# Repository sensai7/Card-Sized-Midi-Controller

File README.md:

# Card Size Midi Controller
 Standard card sized MIDI controller, for level, pan, modulation wheel and control changes. Both hardware and software are open source, you can modify and use as you please.

## Ordering your own board
### Tindie

This device is available at [Tindie](https://www.tindie.com/products/sensai7/card-sized-midi-controller/).

### JLCPCB
This repository includes the necessary files to order your own board with the SMT components pre-soldered from JLCPCB's assembly service. To do so, follow this: 

1. from this Github page click `Code > download zip`.
2. Uncompress the zip.
3. Go to jlcpcb.com or any other pcb maker. I'll assume you're using JLC for the next steps.
4. Select `instant quote` and when prompted to select a gerber file, select the file `\Kicad\CardSizeMidiController\production\CardSizeMidiController.zip`. From here there will be a lot of options but most of them can be left as default. The only “mandatory” change is `Mark on PCB` which should be changed to `Order Number (Specify Position)`. You can also optionaly change:
* the quantity (5 by default)
* the color, which is green by default.
* PCB thickness can also be changed at will but I think too thin or too thick and the price increases a little bit.

If you go like this and checkout the order you will be buying the naked PCBs with nothing mounted. If you want at least to mount the SMT components then:

1. Switch the PCB Assembly on at the bottom of the menu in the JLC order page.
2. Everything can be left on the default values (Top side, Economic, etc) but you can choose to assemble just a couple of boards instead of all of them. It’ll save you some money but you’ll be left with 3 naked boards.
3. Hit next twice and you'll be asked to upload a BOM file and a CPL file. They’re both in the same folder as the gerber zip from before, they’re respectively `bom.csv` and `positions.csv`.
4. Go to the next screen and you’ll see a table with all the components that are about to be assembled.
5. Next screen will show you a 3D render of the board with the components. For some reason Kicad doesn't export all well the positions and angles, so keep an eye on where the things are being placed. Particularly the position of the USB connector, the potentiometers, and the angle of the push buttons.
6. After that screen you can continue until ordering them.

## Writing the firmware

To burn the firmware you'll need an Arduino Uno board or any Arduino that can be used as ISP. 

 1. Upload the Arduino example "Arduino as ISP" to your arduino board.
 2. Unplug the Arduino, connect the ICSP header from the Arduino to the ICSP header of your MIDI controller board, EXCEPT the RST pin from the MIDI controller (third row, first column), which should be connected to the arduino board pin 10.

 3. Check which processor you have. If you have an AtMega328P you can continue, if it's a AtMega328PB you'll need to [change the signature](https://www.instructables.com/How-to-Fix-Expected-Signature-for-ATMEGA328P-Is-1E/) in the avrdude config file.
 3. In tools > Programmer be sure "Arduino as ISP" is selected with a check mark, or otherwhise the following actions will be executed in the Arduino board instead of the target board.
 4. Select the appropiate board/port in the Arduino IDE and go to tools > Burn bootloader. This bootloader will be overwritten in a second, but burning it now will activate some useful fuses inside the microcontroller, particularly the one selecting an external crystal oscillator. This needs to be done only once per chip.
 5. Open the firmware script "\Code\CardSizeMidiController\CardSizeMidiController.ino" or any custom script in the Arduino IDE and holding shift press the upload button, or select Sketch > Upload using uploader. After a few seconds of LED flashing the chip should have the firmware ready.

## How to use (Standard firmware)
Each button selects a different mode. The turned on LEDs signal the active midi channels.

 * When LEVEL mode is activated, each potentiometer change the Level Control Change (0x07) from channels 1 to 6.
 * When PAN mode is activated, each potentiometer change the Pan Control Change (0x0A) from channels 1 to 6.
 * When MOD mode is activated, each potentiometer change the Modulation Wheel Control Change (0x01) from channels 1 to 6.
 * When CC1 mode is activated, each potentiometer change a different unassigned CC value (0x1A,0x1B,0x1C,0x1D,0x1E,0x1F) in the active channel. 
 * When CC1 mode is activated, each potentiometer change a different unassigned CC value (0x66,0x67,0x68,0x69,0x70,0x71) in the active channel. 
 * When CC1 mode is activated, each potentiometer change a different unassigned CC value (0x72,0x73,0x74,0x75,0x76,0x77) in the active channel. 

In the CC modes the midi channel can be changed from 1 to 16 pressing multiple times the same button. The LEDs light up accordingly.
In the LEVEL, PAN, and MOD modes, subsequent presses of the mode button will toggle the active MIDI channels from 1-6 to 7-12.

There are currently three double-button press settings:

 * Holding down buttons 1 and 2 makes the rightmost potentiometer control the value randomness from 0 (not randomness) to 127 (any value possible).
 * Holding down buttons 3 and 4 makes the rightmost potentiometer change the curve for all the MIDI messages from linear to logarithmic.
 * Holding down buttons 5 and 6 makes the rightmost potentiometer control the LED brightness.

Hold down a switch while powering up to select a different CC preset (1~6). Different presets can be flashed via code to accomodate to the CC received by any synthesizer or audio device. Not pressing any switch during boot will result in the default CC preset, which uses the forementioned undefined CC values.

Default presets:

 0. (default) Undefined CC. Use this preset to use along MIDI learn in your devices.
 1. Korg Volca FM preset
 2. Korg Volca Keys preset
 3. Korg Volca Bass preset
 4. Korg Volca Nubass preset
 5. Korg Volca Kick preset
 6. Korg Volca Sample preset

## How to use (Korg NTS-3 firmware)
This firmware allows more functionality when used along with a Korg NTS-3 kaoss pad kit. In this firmware the controls act like follow:

 * Pressing the 1st push button, enters FX1 mode. In this mode the potentiometers change Control changes (16, 48, 17, 49, 18, 50), corresponding to PADX (coarse), PADX (fine), PADY (coarse), PADY (fine), DEPTH (coarse), and DEPTH (fine) respectively, for FX1
 * Pressing buttons 2, 3 and 4 change the mode to FX2, FX3 and FX4 respectively. The potentiometer controls are arranged the same as in FX1 mode except they affect the corresponding mode FX number.
 * Button 5 changes the mode to TOTAL FX mode, the potentiometer controls are arranged the same as in FX1~4 but they affect the total FX.
 * Button 6 changes the mode to MASTER AND SELECTION mode, in this mode the potentiometers control Master Volume (coarse), Master Volume (fine), FX1 SELECTION, FX2 SELECTION, FX3 SELECTION, and FX4 SELECTION respectively.
 * In modes FX1~4, successive button presses freeze and unfreeze the selected FX, this is reflected by the brightness of the selected mode LED.

 Along with the three double-button settings present in the regular firmware (Randomness, linear-log setting, and LED brightness), there are extra double-button controls:

 * While holding Button 5, pressing buttons 1 to 4 toggle FX1 to 4 TOUCH on and off.
 * While holding Button 6, pressing buttons 1 to 4 toggle FX1 to 4 on and off.

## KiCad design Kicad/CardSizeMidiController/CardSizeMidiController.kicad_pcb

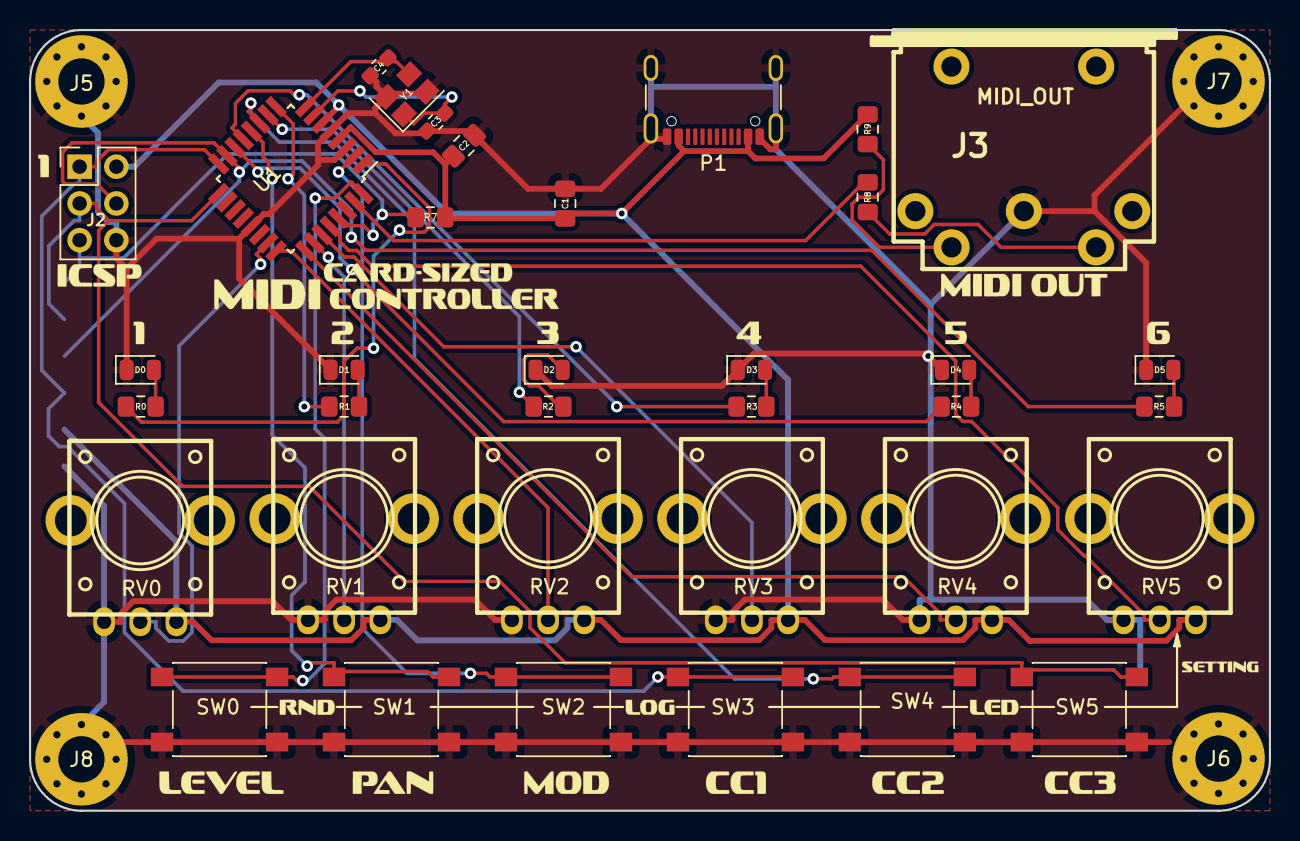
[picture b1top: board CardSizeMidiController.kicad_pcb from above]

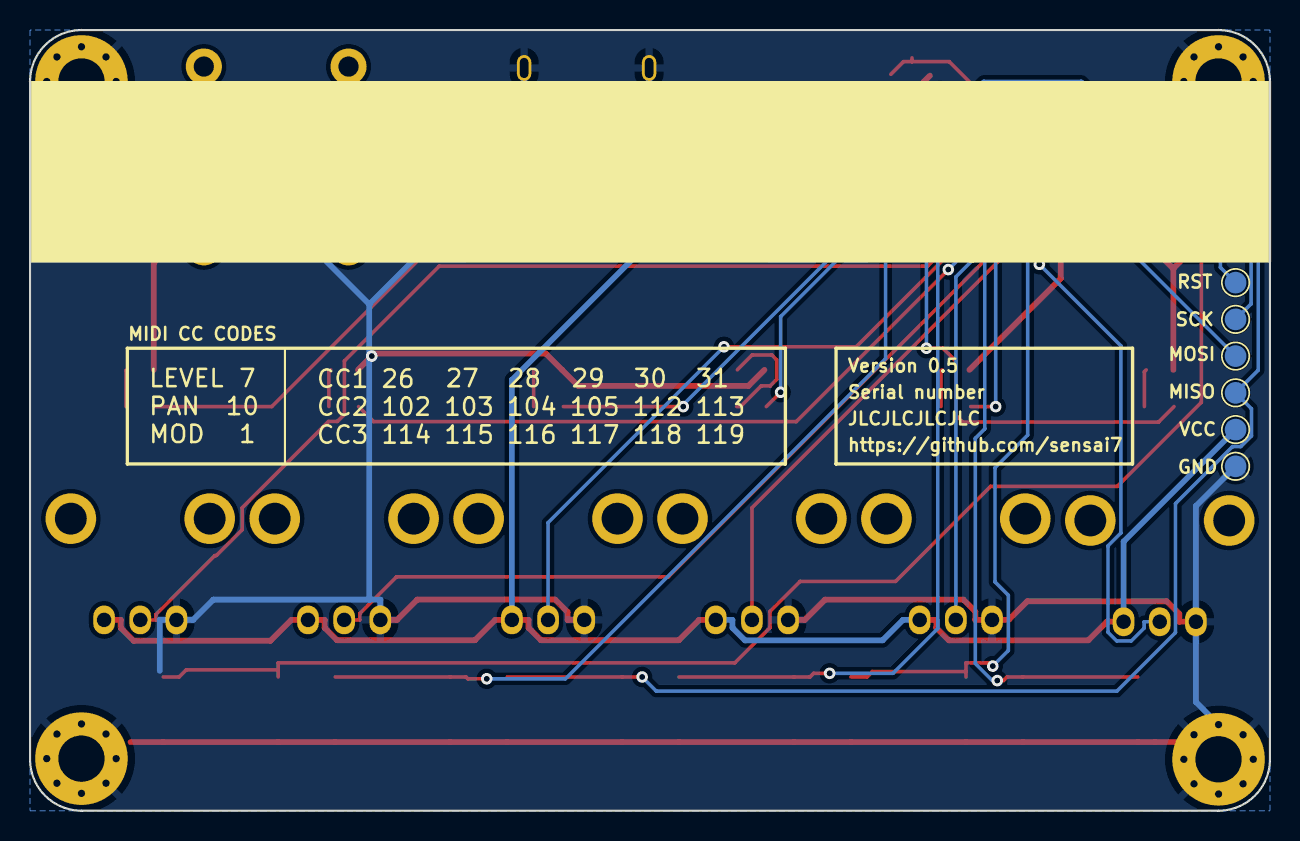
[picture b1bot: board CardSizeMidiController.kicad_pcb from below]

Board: 2 copper layers, 85.7 x 54.0 mm, 66 parts (6 on the bottom side), 32 nets.

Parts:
C1: 100n; C_0805_2012Metric_Pad1.15x1.40mm_HandSolder
C2: 10u; C_0805_2012Metric_Pad1.15x1.40mm_HandSolder
C3, C4: 22p; C_0603_1608Metric_Pad1.05x0.95mm_HandSolder
D0, D1, D2, D3, D4, D5: LED; LED_0805_2012Metric
J2: Conn_02x03_Odd_Even; PinHeader_2x03_P2.54mm_Vertical
J3: MIDI_OUT; din-5
J5, J6, J7, J8: Screw_Terminal_01x01; MountingHole_3.2mm_M3_Pad_Via
LOGO1: Logo_Open_Hardware_Small; card sized midi controller logo
LOGO2: Logo_Open_Hardware_Small; ICSP
LOGO3: Logo_Open_Hardware_Small; midi out
LOGO4: Logo_Open_Hardware_Small; setting
LOGO5: Logo_Open_Hardware_Small; rnd
LOGO6: Logo_Open_Hardware_Small; log
LOGO7: Logo_Open_Hardware_Small; led
LOGO8, LOGO14: Logo_Open_Hardware_Small; 1
LOGO9: Logo_Open_Hardware_Small; 2
LOGO10: Logo_Open_Hardware_Small; 3
LOGO11: Logo_Open_Hardware_Small; 4
LOGO12: Logo_Open_Hardware_Small; 5
LOGO13: Logo_Open_Hardware_Small; 6
LOGO15: Logo_Open_Hardware_Small; level
LOGO16: Logo_Open_Hardware_Small; pan
LOGO17: Logo_Open_Hardware_Small; mod
LOGO18: Logo_Open_Hardware_Small; cc1
LOGO19: Logo_Open_Hardware_Small; cc2
LOGO20: Logo_Open_Hardware_Small; cc3
P1: USB_C_Plug_USB2.0; USB_C_Receptacle_GCT_USB4105-xx-A_16P_TopMnt_Horizontal
R0, R1, R2, R3, R4, R5: 1k; R_0805_2012Metric_Pad1.15x1.40mm_HandSolder
R7: 10k; R_0805_2012Metric_Pad1.15x1.40mm_HandSolder
R8, R9: 220R; R_0805_2012Metric_Pad1.15x1.40mm_HandSolder
RV0, RV1, RV2, RV3, RV4, RV5: 5k; trimmer_alps-rk09k1130ah1
SW0, SW1, SW2, SW3, SW4, SW5: SW_Push; SW_Push_1P1T_NO_6x6mm_H9.5mm
TP1, TP2, TP3, TP4, TP5, TP6: TestPoint; TestPoint_Pad_D1.5mm
U1: ATmega328P-AU; TQFP-32_7x7mm_P0.8mm
Y1: 16MHz; Crystal_SMD_3225-4Pin_3.2x2.5mm

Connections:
+5V: C1.1, C2.1, J2.2, P1.A4 (VBUS), P1.A9 (VBUS), P1.B4 (VBUS), P1.B9 (VBUS), R7.1, R9.1, RV0.3, RV1.3, RV2.3, RV3.3, RV4.3, RV5.3, TP4.1, U1.4 (VCC), U1.6 (VCC)
A0: RV0.2, U1.23 (PC0)
A1: RV2.2, U1.24 (PC1)
A2: RV4.2, U1.25 (PC2)
A3: RV1.2, U1.26 (PC3)
A4: RV3.2, U1.27 (PC4)
A5: RV5.2, U1.28 (PC5)
GND: C1.2, C2.2, C3.1, C4.2, D0.1 (K), D1.1 (K), D2.1 (K), D3.1 (K), D4.1 (K), D5.1 (K), J2.6, J3.2, J5.1, J6.1, J7.1, J8.1, P1.A1 (GND), P1.A12 (GND), P1.B1 (GND), P1.B12 (GND), P1.S1 (SHIELD), RV0.1, RV1.1, RV2.1, RV3.1, RV4.1, RV5.1, SW0.2, SW1.2, SW2.2, SW3.2, SW4.2, SW5.2, TP6.1, U1.3 (GND), U1.5 (GND), U1.21 (GND), Y1.2, Y1.4
LED0: R0.1, U1.1 (PD3)
LED1: R1.1, U1.9 (PD5)
LED2: R2.1, U1.10 (PD6)
LED3: R3.1, U1.13 (PB1)
LED4: R4.1, U1.14 (PB2)
LED5: J2.4, R5.1, TP5.1, U1.15 (PB3)
MISO: J2.1, SW3.1, TP1.1, U1.16 (PB4)
unnamed: D0.2 (A), R0.2
unnamed: D1.2 (A), R1.2
unnamed: D2.2 (A), R2.2
unnamed: D3.2 (A), R3.2
unnamed: D4.2 (A), R4.2
unnamed: D5.2 (A), R5.2
unnamed: J3.4, R9.2
unnamed: J3.5, R8.1
SCK: J2.3, SW5.1, TP2.1, U1.17 (PB5)
SW0: SW0.1, U1.32 (PD2)
SW1: SW2.1, U1.2 (PD4)
SW2: SW4.1, U1.11 (PD7)
SW3: SW1.1, U1.12 (PB0)
TX: R8.2, U1.31 (PD1)
XTAL1: C3.2, U1.7 (XTAL1/PB6), Y1.1
XTAL2: C4.1, U1.8 (XTAL2/PB7), Y1.3
~RST: J2.5, R7.2, TP3.1, U1.29 (~RESET/PC6)

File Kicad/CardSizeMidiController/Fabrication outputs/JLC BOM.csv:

Comment,Designator,Footprint,LCSC
100n,C1,Capacitor_SMD:C_0805_2012Metric_Pad1.15x1.40mm_HandSolder,C49678
10u,C2,Capacitor_SMD:C_0805_2012Metric_Pad1.15x1.40mm_HandSolder,C15850
22p,"C3,C4",Capacitor_SMD:C_0603_1608Metric_Pad1.05x0.95mm_HandSolder,C1653
LED,"D0,D1,D2,D3,D4,D5",LED_SMD:LED_0805_2012Metric,C34499
USB_B,J1,Connector_USB:USB_B_OST_USB-B1HSxx_Horizontal,C490687
1k,"R0,R1,R2,R3,R4,R5",Resistor_SMD:R_0805_2012Metric_Pad1.15x1.40mm_HandSolder,C17513
10k,R7,Resistor_SMD:R_0805_2012Metric_Pad1.15x1.40mm_HandSolder,C17414
220R,"R8,R9",Resistor_SMD:R_0805_2012Metric_Pad1.15x1.40mm_HandSolder,C17557
100k,"RV0,RV1,RV2,RV3,RV4,RV5",w_pth_resistors:trimmer_alps-rk09k1130ah1,C202373
SW_Push,"SW0,SW1,SW2,SW3,SW4,SW5",Button_Switch_SMD:SW_Push_1P1T_NO_6x6mm_H9.5mm,C127509
ATmega328P-AU,U1,Package_QFP:TQFP-32_7x7mm_P0.8mm,C14877
16MHz,Y1,Crystal:Crystal_SMD_3225-4Pin_3.2x2.5mm,C13738

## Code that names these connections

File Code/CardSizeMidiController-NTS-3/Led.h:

#ifndef LED_H
#define LED_H

#include <Arduino.h>

// Pin definitions
#define LED0 3
#define LED1 5
#define LED2 6
#define LED3 9
#define LED4 10
#define LED5 11
// Other macros
#define DEFAULT_BRIGHTNESS 30

// Led class definition
class Led {
private:
  uint8_t pin;
  bool status;
  uint8_t brightness;
  unsigned long startTime;
  unsigned long duration;
  bool isTiming;

public:
  // Constructor
  Led(uint8_t pin, uint8_t brightness = DEFAULT_BRIGHTNESS);

  // Getters / setters
  bool getStatus();

  // Methods
  void turnOn();
  void turnOff();
  void turnTo(bool status);
  void toggle();
  void setBrightness(uint8_t newBrightness);
  void lightFor(unsigned long duration);
  void update();
};

#endif

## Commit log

2020-12-19 pcb layout changes
2020-12-19 Update CardSizeMidiController.kicad_pcb
    silkscreen changes
2020-12-19 Update CardSizeMidiController.ino
    changed harcoded value into its own variable
2020-12-19 layout adjustments
2020-12-20 Autorouted
2020-12-20 layout modifications
2020-12-20 Readme first version
2020-12-21 Added gerber files, bom and position, edited readme
2021-01-04 Increased PWM frequency in 3/9/10/11 to avoid flickering
2021-01-04 small gerber changes
2021-01-04 Fix JLCPCB quote link in README to be absolute
    Otherwise the readme attempts to link to a path relative to the repo on GitHub
2021-01-04 turns out the increased pwm frequency isn't necessary if the crystal oscillator is working
2021-01-06 simplified midi code, addeed dual functions, added led brightness adjust, added randomness option
2021-01-06 small layout changes
2021-01-06 added log response setting
2021-01-07 code cleanup, final double push functionality
2021-01-07 new silkscreen design, created logo and labels, minor layout changes
2021-01-08 small changes to back silkscreen
2021-01-30 changed caps to smd
2021-01-31 added CC presets
2021-01-31 added Volca FM CC preset
2021-01-31 New pic / Added preset explanation
2021-01-31 removed capacitors from BOM as they are now SMT
2021-02-04 Added comments for volcaFMCC1[SIX],volcaFMCC2[SIX]
2021-02-04 Added CC presets for Volca Keys Corrected CC3 = volcaFMCC2 --> CC3 = volcaFMCC3
2021-02-05 Added CC preset for Volca Bass
2021-02-05 Corrected volcaKBassCC3[SIX] --> volcaBassCC3[SIX] set all CCs in volcaBassCC3[SIX] to 0x01
2021-02-05 Added CC preset for Volca Nubass
2021-02-05 Added CC preset for Volca Kick
2021-02-05 Added CC preset for Volca Sample
2021-02-05 added control over midi channels 7~12 for level, pan and mod
2021-02-05 todo list added
2021-02-05 new features info
2021-02-22 fixed a but that caused wrong midi cc sends
2021-04-12 Added Korg NTS-1 alternative firmware
2021-04-12 fixed init mode bug
2021-09-13 v0.4
2021-09-24 changes for new version
2023-08-20 added a small explanation to the programming section
2024-09-10 0.5 hardware and new code wip
2024-09-10 finished code
2024-09-11 back to old functionality but with new hat
2024-09-12 fixed led bug, changed map with shift
2024-09-12 new image
2024-09-14 newest fabrication 0.5
2024-09-14 removed backups
2024-09-14 removed matlab drive things
2024-09-14 updated gitignore
2024-09-16 Changed midi connector for size restrictions
2024-09-16 Fixed switch rotation
2024-09-16 Update pot positions
2024-09-17 Added more detailed explanation on how to order
2024-12-04 Added NTS-3 firmware
2024-12-26 added new pot median method
